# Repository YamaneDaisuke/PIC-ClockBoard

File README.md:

# PIC-ClockBoard
ClockBordドライバ用プログラム
プラットフォームは PIC16F877Aで動作

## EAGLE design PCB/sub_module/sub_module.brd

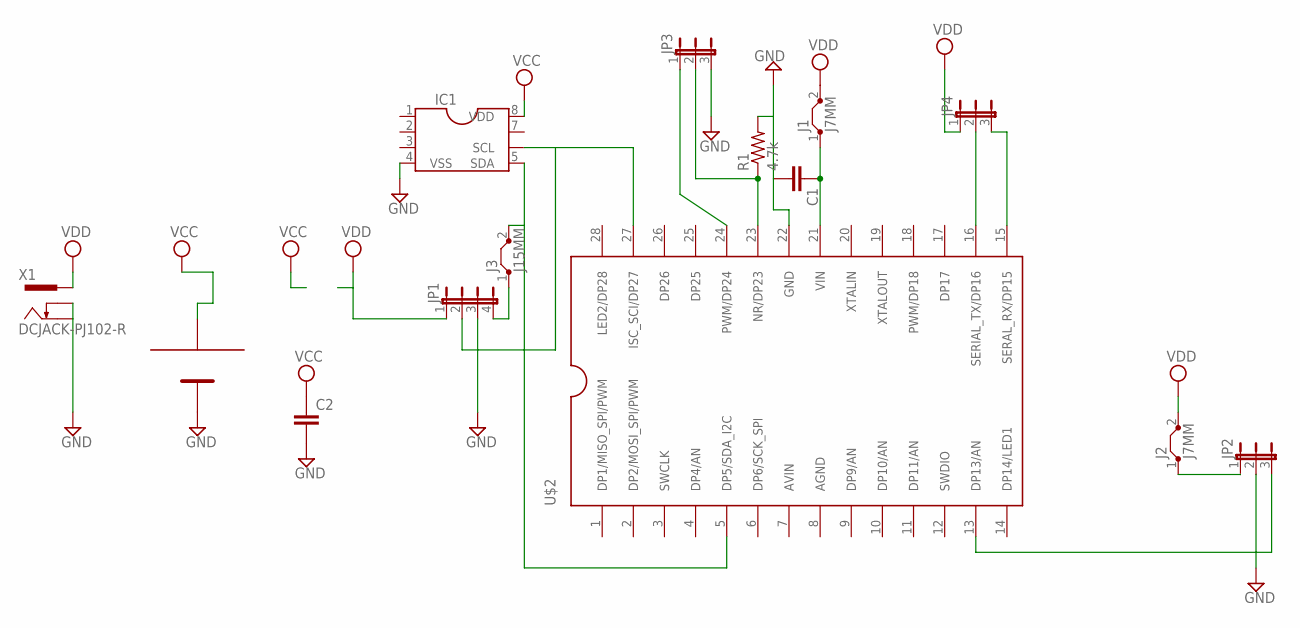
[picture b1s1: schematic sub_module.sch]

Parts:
C1, C2: C-EUC2012; C2012
IC1: DIL8S; SOCKET-08
J1, J2: J7MM; 07
J3: J15MM; 15
JP1: JP4E; JP4
JP2, JP3, JP4: JP2E; JP2
R1: 4.7k; 0207/2V
U$1: CR2032-HOLDER2
U$2: LPC1114FDH28; TSSOP28
X1: DCJACK-PJ102-R; PJ-102-R

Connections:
AGND: U$2.8 (AGND)
AVIN: U$2.7 (AVIN)
GND: C1.2, C2.2, IC1.4 (VSS), JP1.3, JP2.2, JP3.3, R1.2, U$1.GND, U$2.22 (GND), X1.2, X1.3
unnamed: IC1.6 (SCL), JP1.2, U$2.27 (ISC_SCI/DP27)
unnamed: IC1.5 (SDA), J3.2, U$2.5 (DP5/SDA_I2C)
unnamed: C1.1, J1.1, U$2.21 (VIN)
unnamed: JP4.3, U$2.15 (SERAL_RX/DP15)
unnamed: J2.1, JP2.1
unnamed: JP2.3, U$2.13 (DP13/AN)
unnamed: JP4.2, U$2.16 (SERIAL_TX/DP16)
unnamed: J3.1, JP1.4
unnamed: JP3.2, R1.1, U$2.23 (NR/DP23)
unnamed: JP3.1, U$2.24 (PWM/DP24)
VCC: C2.1, IC1.8 (VDD), U$1.+3V
VDD: J1.2, J2.2, JP1.1, JP4.1, X1.1

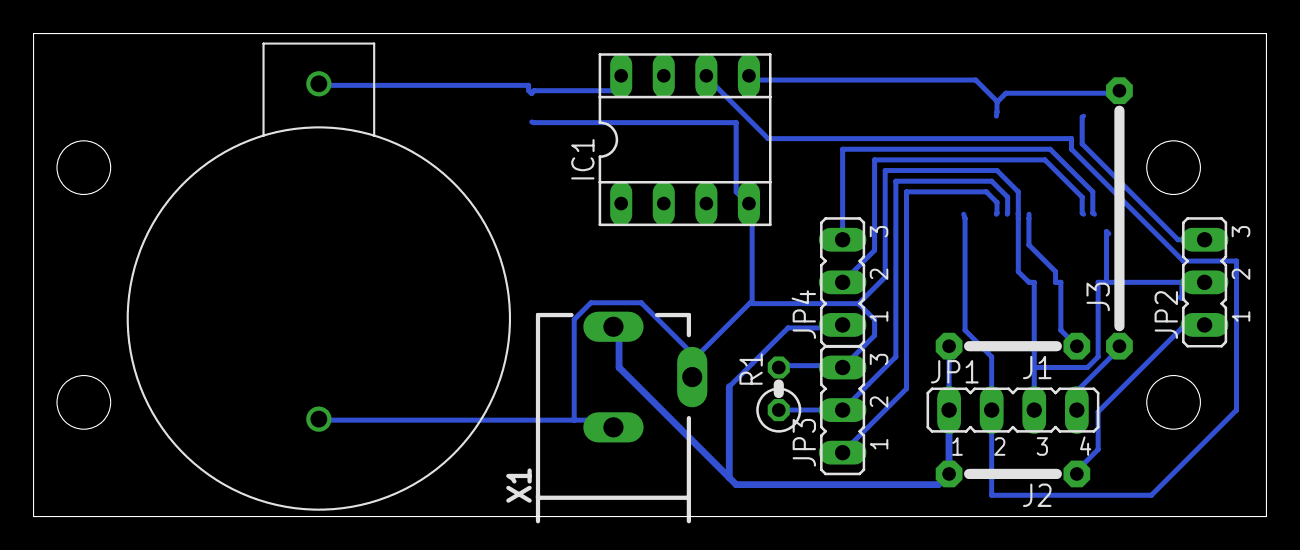
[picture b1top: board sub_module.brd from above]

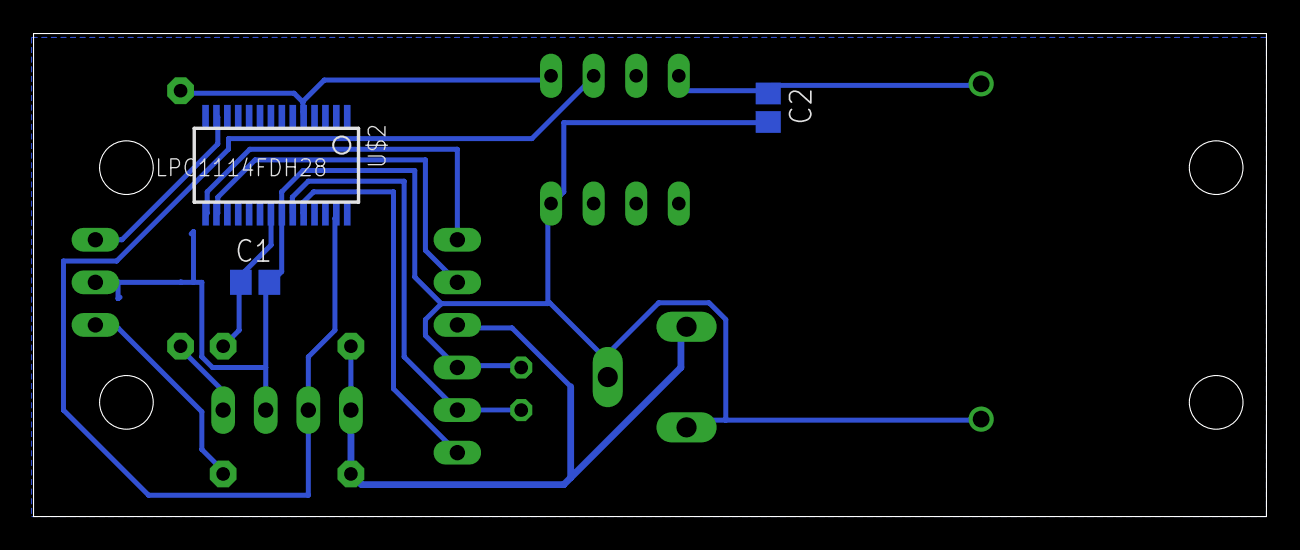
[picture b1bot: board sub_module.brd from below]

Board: 2 copper layers, 73.5 x 28.8 mm, 14 parts (3 on the bottom side), 13 nets.

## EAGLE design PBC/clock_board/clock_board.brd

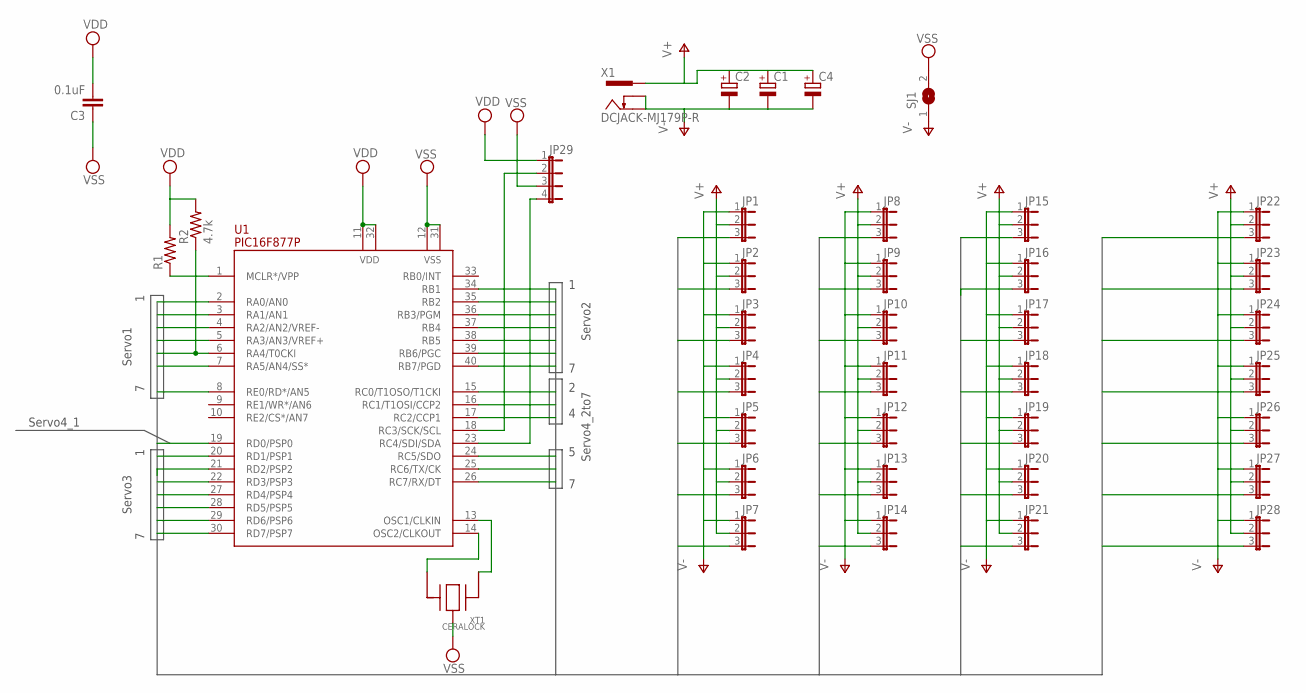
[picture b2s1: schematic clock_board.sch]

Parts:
C1, C2, C4: CPOL-EUE2.5-5; E2,5-5
C3: 0.1uF; C025-024X044
JP1, JP2, JP3, JP4, JP5, JP6, JP7, JP8, JP9, JP10, JP11, JP12, JP13, JP14, JP15, JP16, JP17, JP18, JP19, JP20, JP21, JP22, JP23, JP24, JP25, JP26, JP27, JP28: JP2E; JP2
JP29: JP4E; JP4
R1: R-US_0207/10; 0207/10
R2: 4.7k; 0207/10
SJ1: SJW
U1: PIC16F877P; DIL40
X1: DCJACK-MJ179P-R; MJ-179P-R
XT1: CERALOCK

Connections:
unnamed: U1.14 (OSC2/CLKOUT), XT1.P$3 (3)
unnamed: U1.13 (OSC1/CLKIN), XT1.P$1 (1)
unnamed: R1.1, U1.1 (MCLR*/VPP)
unnamed: JP29.2, U1.18 (RC3/SCK/SCL)
unnamed: JP29.4, U1.23 (RC4/SDI/SDA)
SERVO0: JP1.3, U1.2 (RA0/AN0)
SERVO1: JP2.3, U1.3 (RA1/AN1)
SERVO2: JP3.3, U1.4 (RA2/AN2/VREF-)
SERVO3: JP4.3, U1.5 (RA3/AN3/VREF+)
SERVO4: JP5.3, R2.1, U1.6 (RA4/T0CKI)
SERVO5: JP6.3, U1.7 (RA5/AN4/SS*)
SERVO6: JP7.3, U1.8 (RE0/RD*/AN5)
SERVO7: JP8.3, U1.34 (RB1)
SERVO8: JP9.3, U1.35 (RB2)
SERVO9: JP10.3, U1.36 (RB3/PGM)
SERVO10: JP11.3, U1.37 (RB4)
SERVO11: JP12.3, U1.38 (RB5)
SERVO12: JP13.3, U1.39 (RB6/PGC)
SERVO13: JP14.3, U1.40 (RB7/PGD)
SERVO14: JP15.3, U1.20 (RD1/PSP1)
SERVO15: JP16.3, U1.21 (RD2/PSP2)
SERVO16: JP17.3, U1.22 (RD3/PSP3)
SERVO17: JP18.3, U1.27 (RD4/PSP4)
SERVO18: JP19.3, U1.28 (RD5/PSP5)
SERVO19: JP20.3, U1.29 (RD6/PSP6)
SERVO20: JP21.3, U1.30 (RD7/PSP7)
SERVO21: JP22.3, U1.19 (RD0/PSP0)
SERVO22: JP23.3, U1.15 (RC0/T1OSO/T1CKI)
SERVO23: JP24.3, U1.16 (RC1/T1OSI/CCP2)
SERVO24: JP25.3, U1.17 (RC2/CCP1)
SERVO25: JP26.3, U1.24 (RC5/SDO)
SERVO26: JP27.3, U1.25 (RC6/TX/CK)
SERVO27: JP28.3, U1.26 (RC7/RX/DT)
V+: C1.+, C2.+, C4.+, JP1.2, JP2.2, JP3.2, JP4.2, JP5.2, JP6.2, JP7.2, JP8.2, JP9.2, JP10.2, JP11.2, JP12.2, JP13.2, JP14.2, JP15.2, JP16.2, JP17.2, JP18.2, JP19.2, JP20.2, JP21.2, JP22.2, JP23.2, JP24.2, JP25.2, JP26.2, JP27.2, JP28.2, X1.1
V-: C1.-, C2.-, C4.-, JP1.1, JP2.1, JP3.1, JP4.1, JP5.1, JP6.1, JP7.1, JP8.1, JP9.1, JP10.1, JP11.1, JP12.1, JP13.1, JP14.1, JP15.1, JP16.1, JP17.1, JP18.1, JP19.1, JP20.1, JP21.1, JP22.1, JP23.1, JP24.1, JP25.1, JP26.1, JP27.1, JP28.1, SJ1.1, X1.2, X1.3
VDD: C3.2, JP29.1, R1.2, R2.2, U1.11 (VDD), U1.32 (VDD)
VSS: C3.1, JP29.3, SJ1.2, U1.12 (VSS), U1.31 (VSS), XT1.P$2 (2)

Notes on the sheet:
Servo1
Servo2
Servo3
Servo4_1
Servo4_2to7

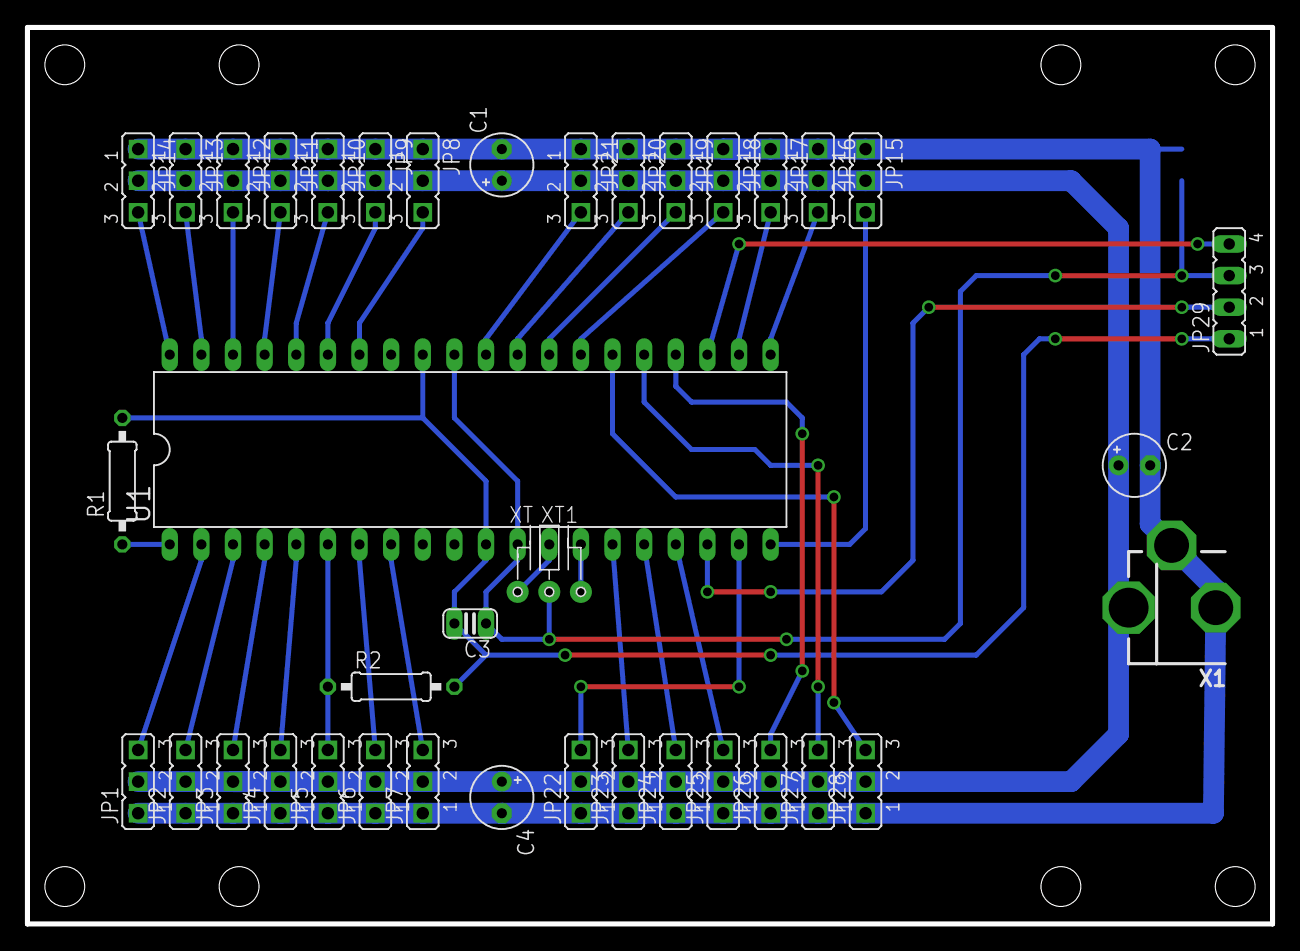
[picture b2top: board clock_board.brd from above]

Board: 2 copper layers, 100.0 x 72.0 mm, 39 parts (1 on the bottom side), 37 nets.

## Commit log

2016-07-16 Add git ignore
2016-07-16 Add liblary and CAM job for Eagle
2016-07-16 Add Program source for PIC16F877A
2016-07-16 Add PBC data
2016-07-21 RA4につながれたサーボモータが動かない不具合を解消
2016-07-22 add sub_board
2016-07-22 Add library
2016-07-24 Add mbed source
2016-08-07 フォルダ名をPBC->PCBに
2016-08-16 rename PBC to PCB
2016-09-10 sub_moduleを改良
2017-05-22 update CR2032 holder
